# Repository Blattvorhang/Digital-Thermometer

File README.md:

# Digital Thermometer
A digital display thermometer based on minisys, including circuit diagram, PCB, single-chip programming as well as data visualisation using Python.

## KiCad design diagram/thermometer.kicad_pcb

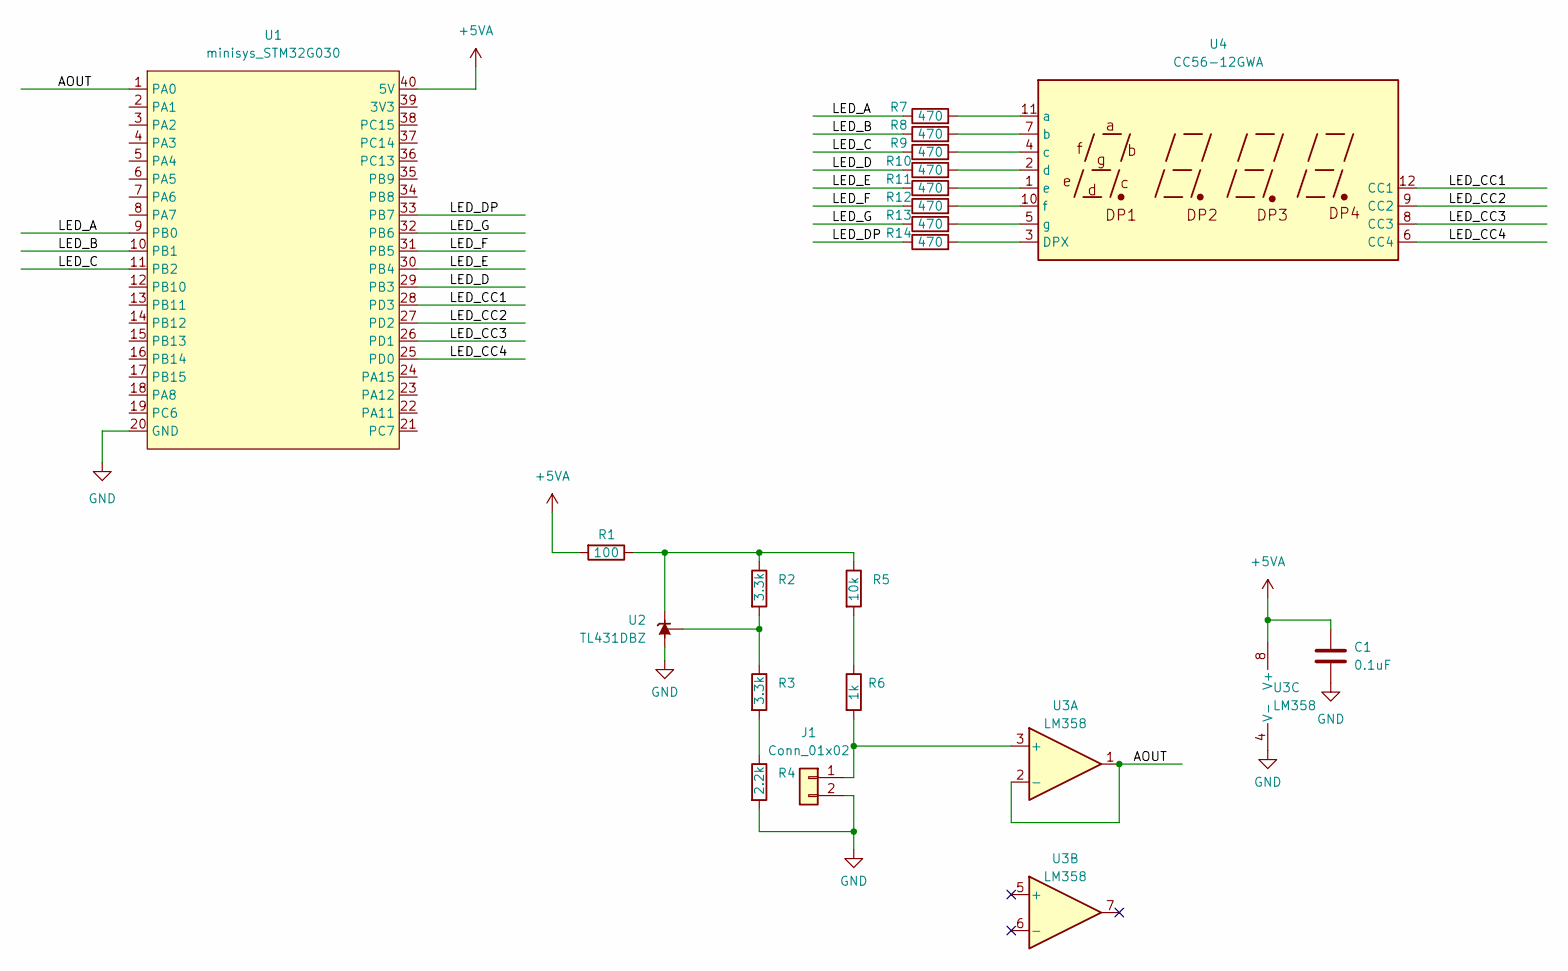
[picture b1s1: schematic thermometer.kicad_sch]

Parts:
C1: 0.1uF; C_0805_2012Metric
J1: Conn_01x02; JST_XH_B2B-XH-A_1x02_P2.50mm_Vertical
R1: 100; R_0805_2012Metric
R2, R3: 3.3k; R_0805_2012Metric
R4: 2.2k; R_0805_2012Metric
R5: 10k; R_0805_2012Metric
R6: 1k; R_0805_2012Metric
R7, R8, R9, R10, R11, R12, R13, R14: 470; R_0805_2012Metric
U1: minisys_STM32G030; minisys_g030
U2: TL431DBZ; SOT-23
U3: LM358; SOIC-8_3.9x4.9mm_P1.27mm
U4: CC56-12GWA; CC40-12GWA

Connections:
+5VA: C1.1, R1.2, U1.40 (5V), U3.8 (V+)
/AOUT: U1.1 (PA0), U3.1, U3.2 (-)
/LED_A: R7.1, U1.9 (PB0)
/LED_B: R8.1, U1.10 (PB1)
/LED_C: R9.1, U1.11 (PB2)
/LED_CC1: U1.28 (PD3), U4.12 (CC1)
/LED_CC2: U1.27 (PD2), U4.9 (CC2)
/LED_CC3: U1.26 (PD1), U4.8 (CC3)
/LED_CC4: U1.25 (PD0), U4.6 (CC4)
/LED_D: R10.1, U1.29 (PB3)
/LED_DP: R14.1, U1.33 (PB7)
/LED_E: R11.1, U1.30 (PB4)
/LED_F: R12.1, U1.31 (PB5)
/LED_G: R13.1, U1.32 (PB6)
GND: C1.2, J1.2, R4.2, U1.20 (GND), U2.3 (A), U3.4 (V-)
unnamed: J1.1, R6.2, U3.3 (+)
unnamed: R1.1, R2.1, R5.1, U2.1 (K)
unnamed: R2.2, R3.1, U2.2 (REF)
unnamed: R3.2, R4.1
unnamed: R5.2, R6.1
unnamed: R7.2, U4.11 (a)
unnamed: R8.2, U4.7 (b)
unnamed: R9.2, U4.4 (c)
unnamed: R10.2, U4.2 (d)
unnamed: R11.2, U4.1 (e)
unnamed: R12.2, U4.10 (f)
unnamed: R13.2, U4.5 (g)
unnamed: R14.2, U4.3 (DPX)

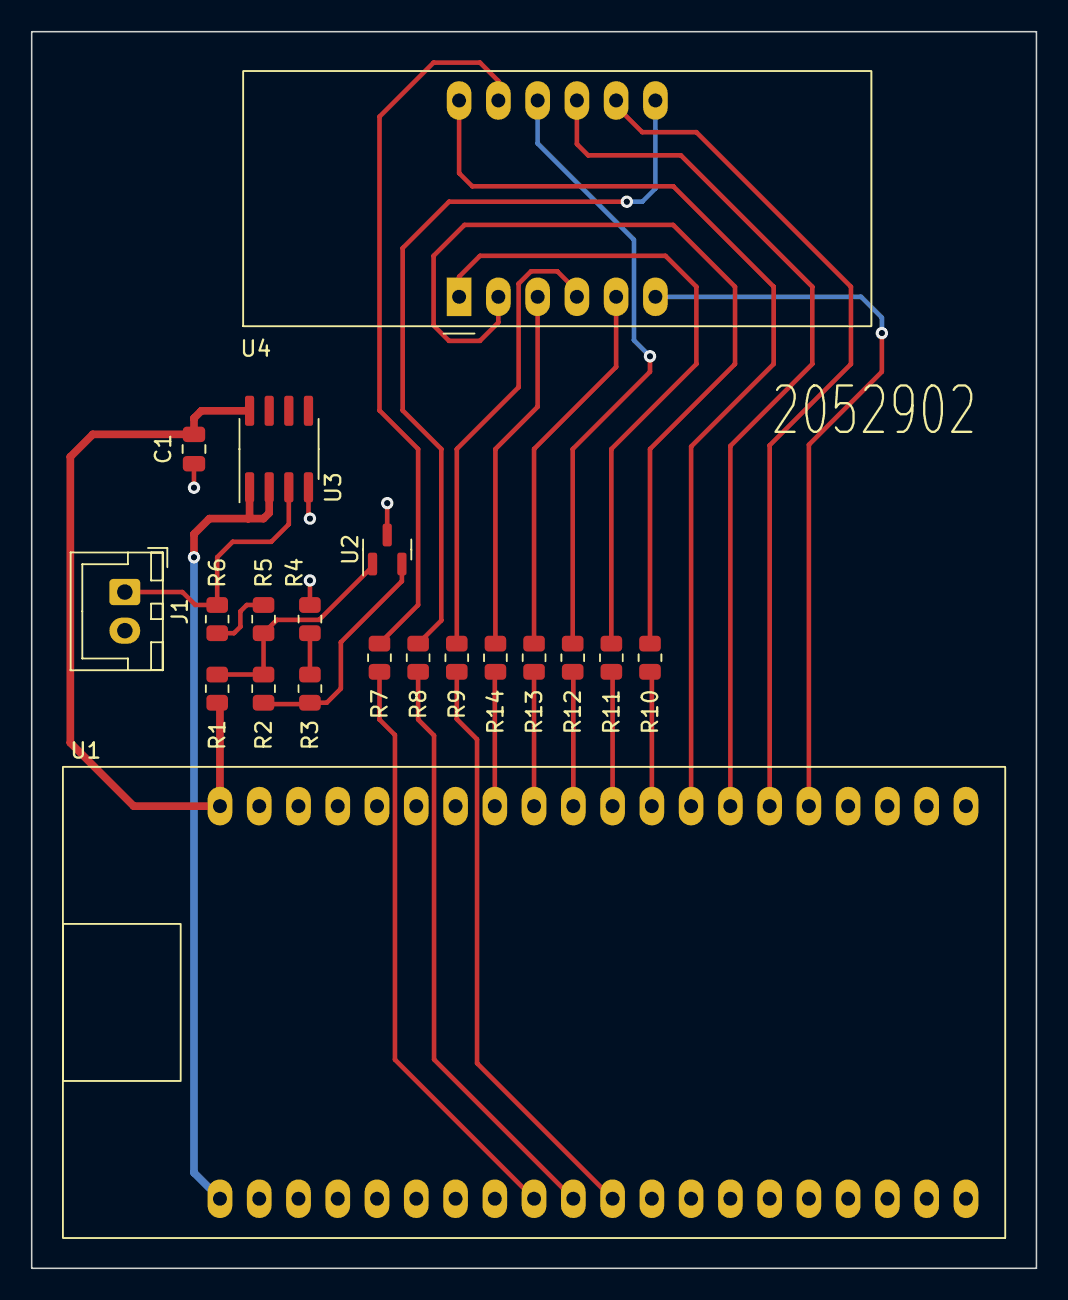
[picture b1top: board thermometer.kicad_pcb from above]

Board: 2 copper layers, 65.0 x 80.0 mm, 20 parts (0 on the bottom side), 28 nets.

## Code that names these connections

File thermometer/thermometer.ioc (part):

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Mcu.Name=STM32G030C(6-8)Tx
Mcu.Package=LQFP48
Mcu.UserName=STM32G030C8Tx
PA0.Mode=IN0
PA0.Signal=ADC1_IN0
PA10.Mode=Asynchronous
PA10.Signal=USART1_RX
PA13.Mode=Serial_Wire
PA13.Signal=SYS_SWDIO
PA14-BOOT0.Mode=Serial_Wire
PA14-BOOT0.Signal=SYS_SWCLK
PA9.Mode=Asynchronous
PA9.Signal=USART1_TX
PB0.GPIOParameters=GPIO_Label
PB0.GPIO_Label=LED_A
PB0.Signal=GPIO_Output
PB1.GPIOParameters=GPIO_Label
PB1.GPIO_Label=LED_B
PB1.Signal=GPIO_Output
PB2.GPIOParameters=GPIO_Label
PB2.GPIO_Label=LED_C
PB2.Signal=GPIO_Output
PB3.GPIOParameters=GPIO_Label
PB3.GPIO_Label=LED_D
PB3.Signal=GPIO_Output
PB4.GPIOParameters=GPIO_Label
PB4.GPIO_Label=LED_E
PB4.Signal=GPIO_Output
PB5.GPIOParameters=GPIO_Label
PB5.GPIO_Label=LED_F
PB5.Signal=GPIO_Output
PB6.GPIOParameters=GPIO_Label
PB6.GPIO_Label=LED_G
PB6.Signal=GPIO_Output
PB7.GPIOParameters=GPIO_Label
PB7.GPIO_Label=LED_H
PB7.Signal=GPIO_Output
PD0.GPIOParameters=PinState,GPIO_PuPd,GPIO_Label,GPIO_ModeDefaultOutputPP
PD0.GPIO_Label=LED_CC4
PD0.GPIO_ModeDefaultOutputPP=GPIO_MODE_OUTPUT_OD
PD0.GPIO_PuPd=GPIO_NOPULL
PD0.PinState=GPIO_PIN_SET
PD0.Signal=GPIO_Output
PD1.GPIOParameters=PinState,GPIO_PuPd,GPIO_Label,GPIO_ModeDefaultOutputPP
PD1.GPIO_Label=LED_CC3
PD1.GPIO_ModeDefaultOutputPP=GPIO_MODE_OUTPUT_OD
PD1.GPIO_PuPd=GPIO_NOPULL
PD1.PinState=GPIO_PIN_SET
PD1.Signal=GPIO_Output
PD2.GPIOParameters=PinState,GPIO_PuPd,GPIO_Label,GPIO_ModeDefaultOutputPP
PD2.GPIO_Label=LED_CC2
PD2.GPIO_ModeDefaultOutputPP=GPIO_MODE_OUTPUT_OD
PD2.GPIO_PuPd=GPIO_NOPULL
PD2.PinState=GPIO_PIN_SET
PD2.Signal=GPIO_Output
PD3.GPIOParameters=PinState,GPIO_PuPd,GPIO_Label,GPIO_ModeDefaultOutputPP
PD3.GPIO_Label=LED_CC1
PD3.GPIO_ModeDefaultOutputPP=GPIO_MODE_OUTPUT_OD
PD3.GPIO_PuPd=GPIO_NOPULL
PD3.PinState=GPIO_PIN_SET
PD3.Signal=GPIO_Output
RCC.HSE_VALUE=8000000
RCC.SYSCLKFreq_VALUE=32000000
RCC.SYSCLKSource=RCC_SYSCLKSOURCE_PLLCLK
board=custom

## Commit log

2023-06-06 add all
